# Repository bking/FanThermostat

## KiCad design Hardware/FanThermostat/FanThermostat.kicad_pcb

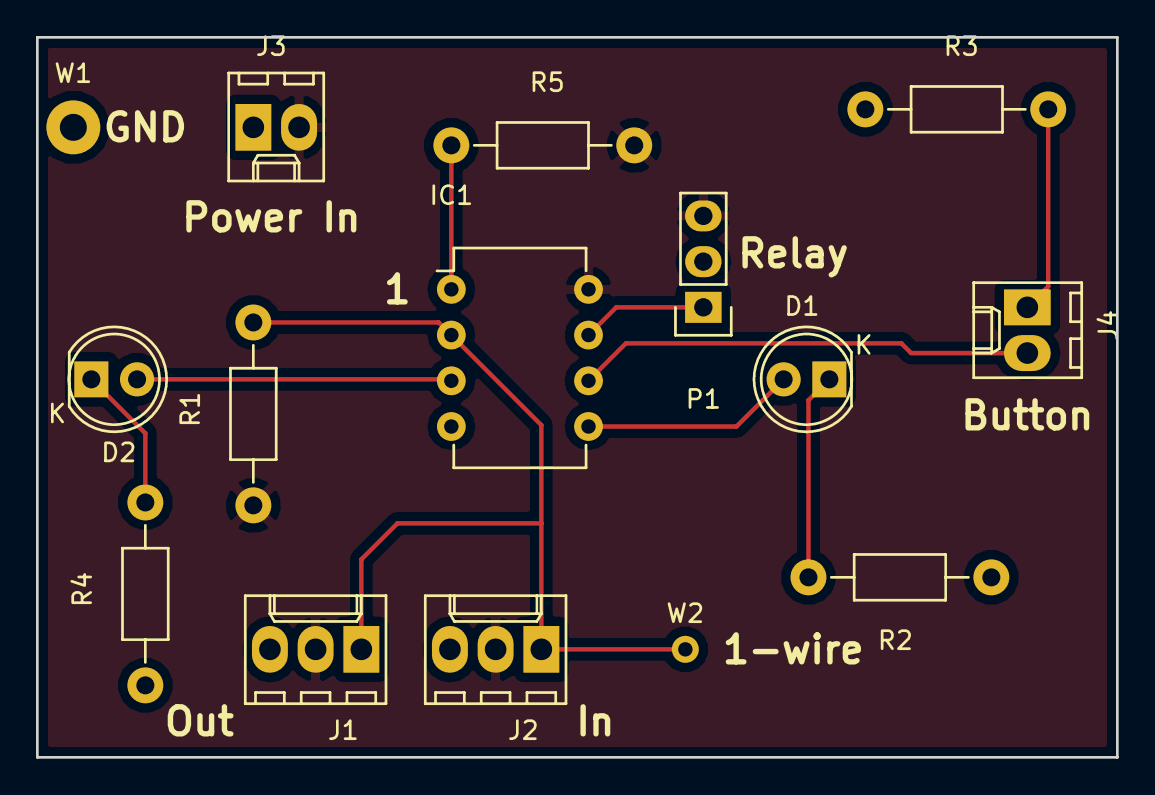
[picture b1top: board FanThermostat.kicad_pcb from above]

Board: 2 copper layers, 60.0 x 40.0 mm, 15 parts (0 on the bottom side), 11 nets.

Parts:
D1, D2: LED; LED-5MM
IC1: ATTINY85-P; DIP-8_W7.62mm
J1: Outside; Molex_KK-6410-03_03x2.54mm_Straight
J2: Inside; Molex_KK-6410-03_03x2.54mm_Straight
J3: Power In; Molex_KK-6410-02_02x2.54mm_Straight
J4: Switch (case); Molex_KK-6410-02_02x2.54mm_Straight
P1: 120V Relay; Pin_Header_Straight_1x03
R1, R2, R3, R4, R5: 4.7k; Resistor_Horizontal_RM10mm
W1: TP G; Measurement_Point_Round-TH_Big
W2: TP 1; Measurement_Point_Round-TH_Small

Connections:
+5V: IC1.8, J1.2, J2.2, J3.2, P1.3, R1.1, R5.2
GND: IC1.4, J1.3, J2.3, J3.1, P1.2, R2.1, R3.1, R4.1, W1.1
unnamed: D1.1, R2.2
unnamed: D1.2, IC1.5
unnamed: D2.1, R4.2
unnamed: D2.2, IC1.3
unnamed: IC1.1, R5.1
unnamed: IC1.2, J1.1, J2.1, R1.2, W2.1
unnamed: IC1.6, J4.2
unnamed: IC1.7, P1.1
unnamed: J4.1, R3.2

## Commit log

2018-07-27 Rename file
2018-07-27 Move stuff around
